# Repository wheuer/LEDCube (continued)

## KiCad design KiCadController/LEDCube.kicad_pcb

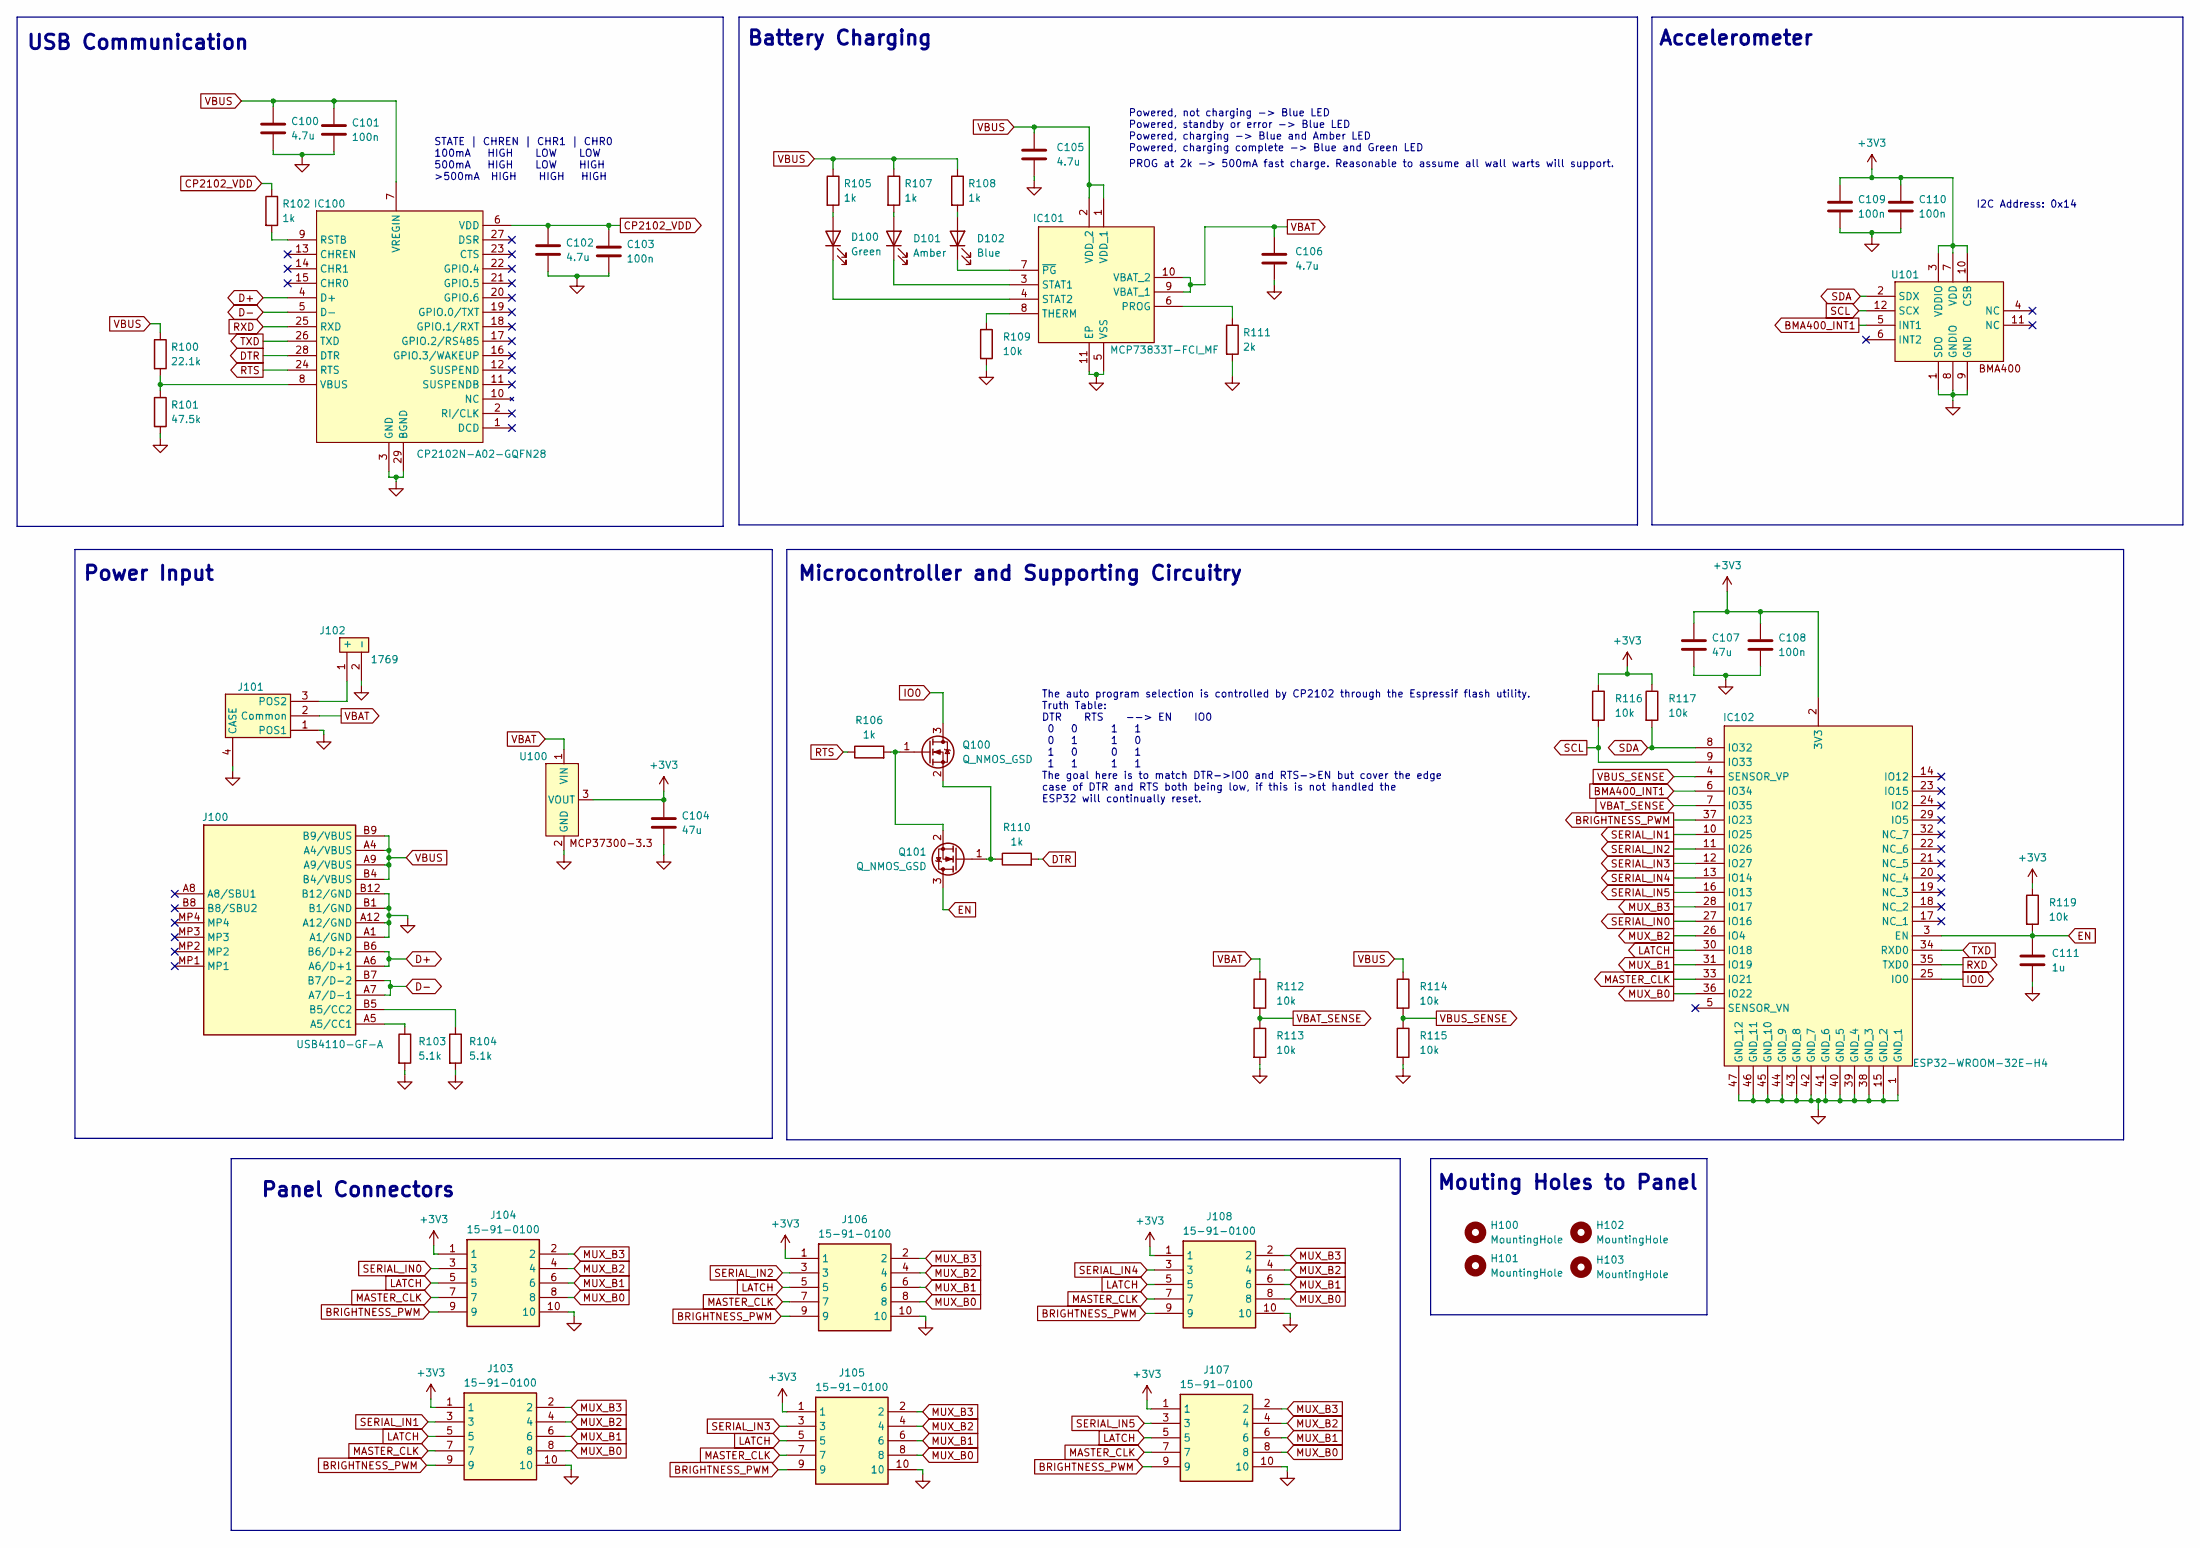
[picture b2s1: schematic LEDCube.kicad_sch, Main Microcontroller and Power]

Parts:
C100, C102, C105, C106: 4.7u; C_0603_1608Metric
C101, C103, C108, C109, C110: 100n; C_0603_1608Metric
C104, C107: 47u; C_1206_3216Metric
C111: 1u; C_0603_1608Metric
D100: Green; LED_0603_1608Metric
D101: Amber; LED_0603_1608Metric
D102: Blue; LED_0603_1608Metric
H100, H101, H102, H103: MountingHole; MountingHole_3.2mm_M3_Pad_Via
IC100: CP2102N-A02-GQFN28; QFN50P500X500X80-29N-D; Mouser Part Number 634-CP2102NA02GQFN28
IC101: MCP73833T-FCI_MF; SON50P300X300X100-11N-D; Mouser Part Number 579-MCP73833T-FCI/MF
IC102: ESP32-WROOM-32E-H4; ESP32WROOM32EH4; Mouser Part Number 356-ESP32WRM320EH3PS
J100: USB4110-GF-A; USB4110GFA; Mouser Part Number 640-USB4110-GF-A
J101: PowerSwitch
J102: 1769; Mouser Part Number 485-1769
J103, J105, J106, J107, J108: 15-91-0100; CNC_TECH_SMD_10POS; Mouser Part Number 538-15-91-0100
J104: 15-91-0100; CNC_TECH_SMD_10POS; Manufacturer_Part_Number 15-91-0100
Q100, Q101: Q_NMOS_GSD; SOT96P237X111-3N
R100: 22.1k; R_0603_1608Metric
R101: 47.5k; R_0603_1608Metric
R102, R105, R106, R107, R108, R110: 1k; R_0603_1608Metric
R103, R104: 5.1k; R_0603_1608Metric
R109, R112, R113, R114, R115, R116, R117, R119: 10k; R_0603_1608Metric
R111: 2k; R_0603_1608Metric
U100: MIC37300-3.3-SPAK3
U101: BOSCH_LGA-12

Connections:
+3V3: C104.1, C107.1, C108.1, C109.1, C110.1, IC102.2 (3V3), J103.1, J104.1, J105.1, J106.1, J107.1, J108.1, R116.1, R117.1, R119.1, U100.3 (VOUT), U101.3 (VDDIO), U101.7 (VDD), U101.10 (CSB)
BMA400_INT1: IC102.6 (IO34), U101.5 (INT1)
BRIGHTNESS_PWM: IC102.37 (IO23), J103.9, J104.9, J105.9, J106.9, J107.9, J108.9
CP2102_VDD: C102.1, C103.1, IC100.6 (VDD), R102.1
D+: IC100.4 (D+), J100.A6 (A6/D+1), J100.B6 (B6/D+2)
D-: IC100.5 (D-), J100.A7 (A7/D-1), J100.B7 (B7/D-2)
DTR: IC100.28 (DTR), R110.2
EN: C111.1, IC102.3 (EN), Q101.3 (D), R119.2
GND: C100.2, C101.2, C102.2, C103.2, C104.2, C105.2, C106.2, C107.2, C108.2, C109.2, C110.2, C111.2, H100.1, H101.1, H102.1, H103.1, IC100.3 (GND), IC100.29 (BGND), IC101.5 (VSS), IC101.11 (EP), IC102.1 (GND_1), IC102.15 (GND_2), IC102.38 (GND_3), IC102.39 (GND_4), IC102.40 (GND_5), IC102.41 (GND_6), IC102.42 (GND_7), IC102.43 (GND_8), IC102.44 (GND_9), IC102.45 (GND_10), IC102.46 (GND_11), IC102.47 (GND_12), J100.A1 (A1/GND), J100.A12 (A12/GND), J100.B1 (B1/GND), J100.B12 (B12/GND), J101.1 (POS1), J101.4 (CASE), J102.2 (-), J103.10, J104.10, J105.10, J106.10, J107.10, J108.10, R101.2, R103.2, R104.2, R109.2, R111.2, R113.2, R115.2, U100.2 (GND), U101.1 (SDO), U101.8 (GNDIO), U101.9 (GND)
IO0: IC102.25 (IO0), Q100.3 (D)
LATCH: IC102.30 (IO18), J103.5, J104.5, J105.5, J106.5, J107.5, J108.5
MASTER_CLK: IC102.33 (IO21), J103.7, J104.7, J105.7, J106.7, J107.7, J108.7
MUX_B0: IC102.36 (IO22), J103.8, J104.8, J105.8, J106.8, J107.8, J108.8
MUX_B1: IC102.31 (IO19), J103.6, J104.6, J105.6, J106.6, J107.6, J108.6
MUX_B2: IC102.26 (IO4), J103.4, J104.4, J105.4, J106.4, J107.4, J108.4
MUX_B3: IC102.28 (IO17), J103.2, J104.2, J105.2, J106.2, J107.2, J108.2
unnamed: D100.2 (A), R105.2
unnamed: D100.1 (K), IC101.4 (STAT2)
unnamed: D101.2 (A), R107.2
unnamed: D101.1 (K), IC101.3 (STAT1)
unnamed: D102.2 (A), R108.2
unnamed: D102.1 (K), IC101.7 (~PG)
unnamed: IC100.9 (RSTB), R102.2
unnamed: IC100.8 (VBUS), R100.2, R101.1
unnamed: IC101.6 (PROG), R111.1
unnamed: IC101.8 (THERM), R109.1
unnamed: J100.A5 (A5/CC1), R103.1
unnamed: J100.B5 (B5/CC2), R104.1
unnamed: J101.3 (POS2), J102.1 (+)
unnamed: Q100.1 (G), Q101.2 (S), R106.2
unnamed: Q100.2 (S), Q101.1 (G), R110.1
RTS: IC100.24 (RTS), R106.1
RXD: IC100.25 (RXD), IC102.35 (TXD0)
SCL: IC102.9 (IO33), R116.2, U101.12 (SCX)
SDA: IC102.8 (IO32), R117.2, U101.2 (SDX)
SERIAL_IN0: IC102.27 (IO16), J104.3
SERIAL_IN1: IC102.10 (IO25), J103.3
SERIAL_IN2: IC102.11 (IO26), J106.3
SERIAL_IN3: IC102.12 (IO27), J105.3
SERIAL_IN4: IC102.13 (IO14), J108.3
SERIAL_IN5: IC102.16 (IO13), J107.3
TXD: IC100.26 (TXD), IC102.34 (RXD0)
VBAT: C106.1, IC101.9 (VBAT_1), IC101.10 (VBAT_2), J101.2 (Common), R112.1, U100.1 (VIN)
VBAT_SENSE: IC102.7 (IO35), R112.2, R113.1
VBUS: C100.1, C101.1, C105.1, IC100.7 (VREGIN), IC101.1 (VDD_1), IC101.2 (VDD_2), J100.A4 (A4/VBUS), J100.A9 (A9/VBUS), J100.B4 (B4/VBUS), J100.B9 (B9/VBUS), R100.1, R105.1, R107.1, R108.1, R114.1
VBUS_SENSE: IC102.4 (SENSOR_VP), R114.2, R115.1

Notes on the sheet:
USB Communication
Accelerometer
Microcontroller and Supporting Circuitry
Mouting Holes to Panel
PROG at 2k -> 500mA fast charge. Reasonable to assume all wall warts will support.
Battery Charging
Panel Connectors
Power Input
Powered, not charging -> Blue LED Powered, standby or error -> Blue LED Powered, charging -> Blue and Amber LED Powered, charging complete -> Blue and Green LED
I2C Address: 0x14
STATE | CHREN | CHR1 | CHR0 100mA HIGH LOW LOW 500mA HIGH LOW HIGH >500mA HIGH HIGH HIGH
The auto program selection is controlled by CP2102 through the Espressif flash utility. Truth Table: DTR RTS --> EN IO0 0 0 1 1 0 1 1 0 1 0 0 1 1 1 1 1 The goal here is to match DTR->IO0 and RTS->EN but cover the edge case of DTR and RTS both being low, if this is not handled the ESP32 will continu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

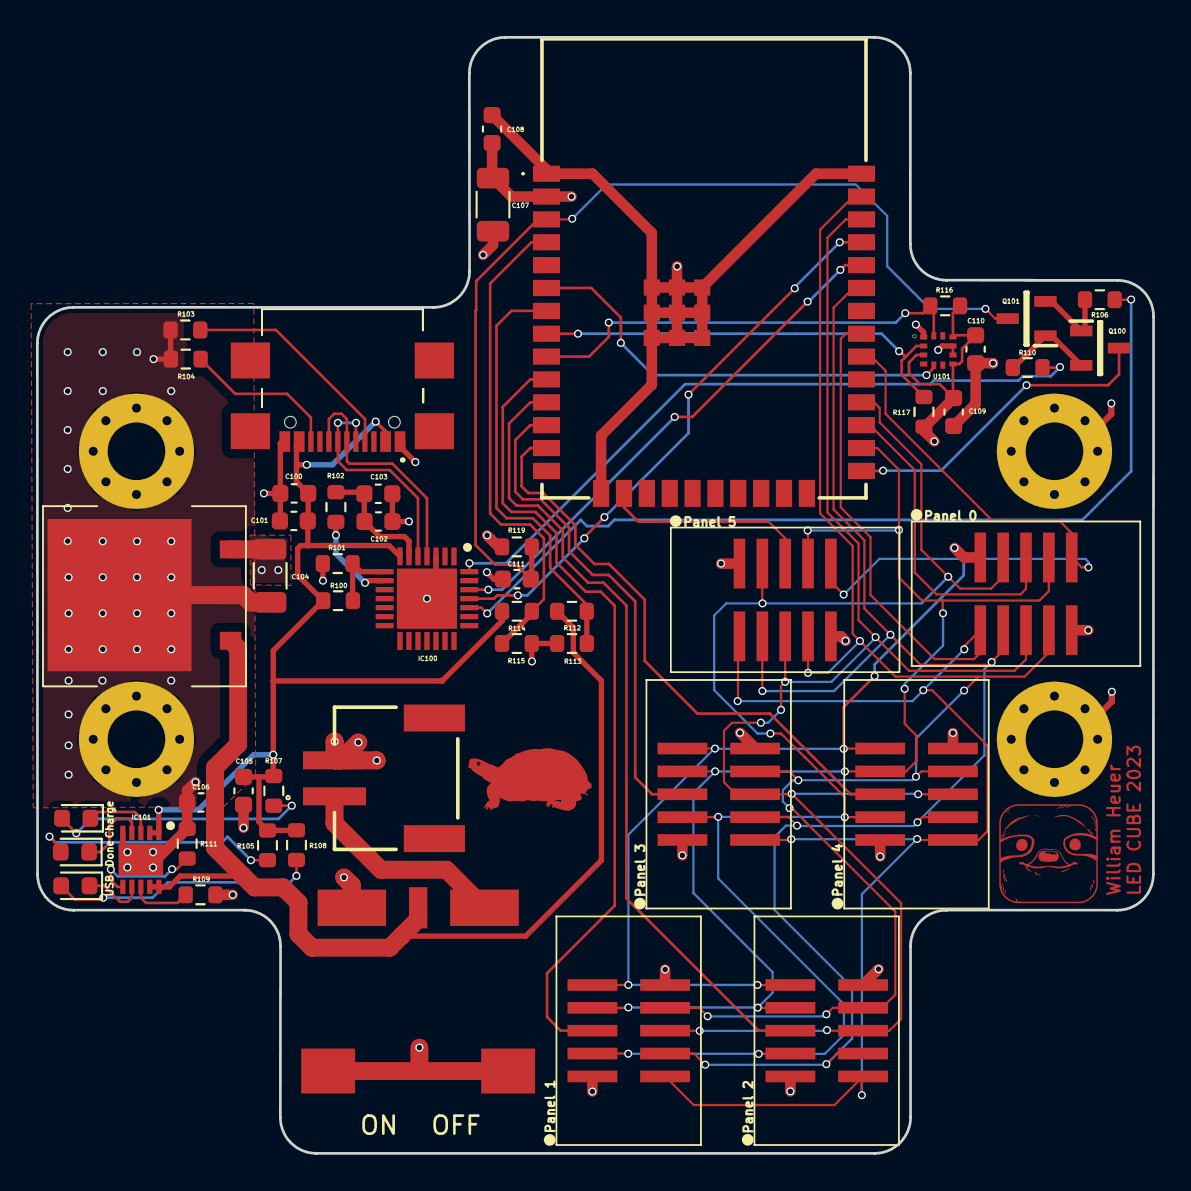
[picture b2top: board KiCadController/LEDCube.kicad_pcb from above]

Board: 4 copper layers, 62.0 x 62.0 mm, 54 parts (0 on the bottom side), 46 nets.
